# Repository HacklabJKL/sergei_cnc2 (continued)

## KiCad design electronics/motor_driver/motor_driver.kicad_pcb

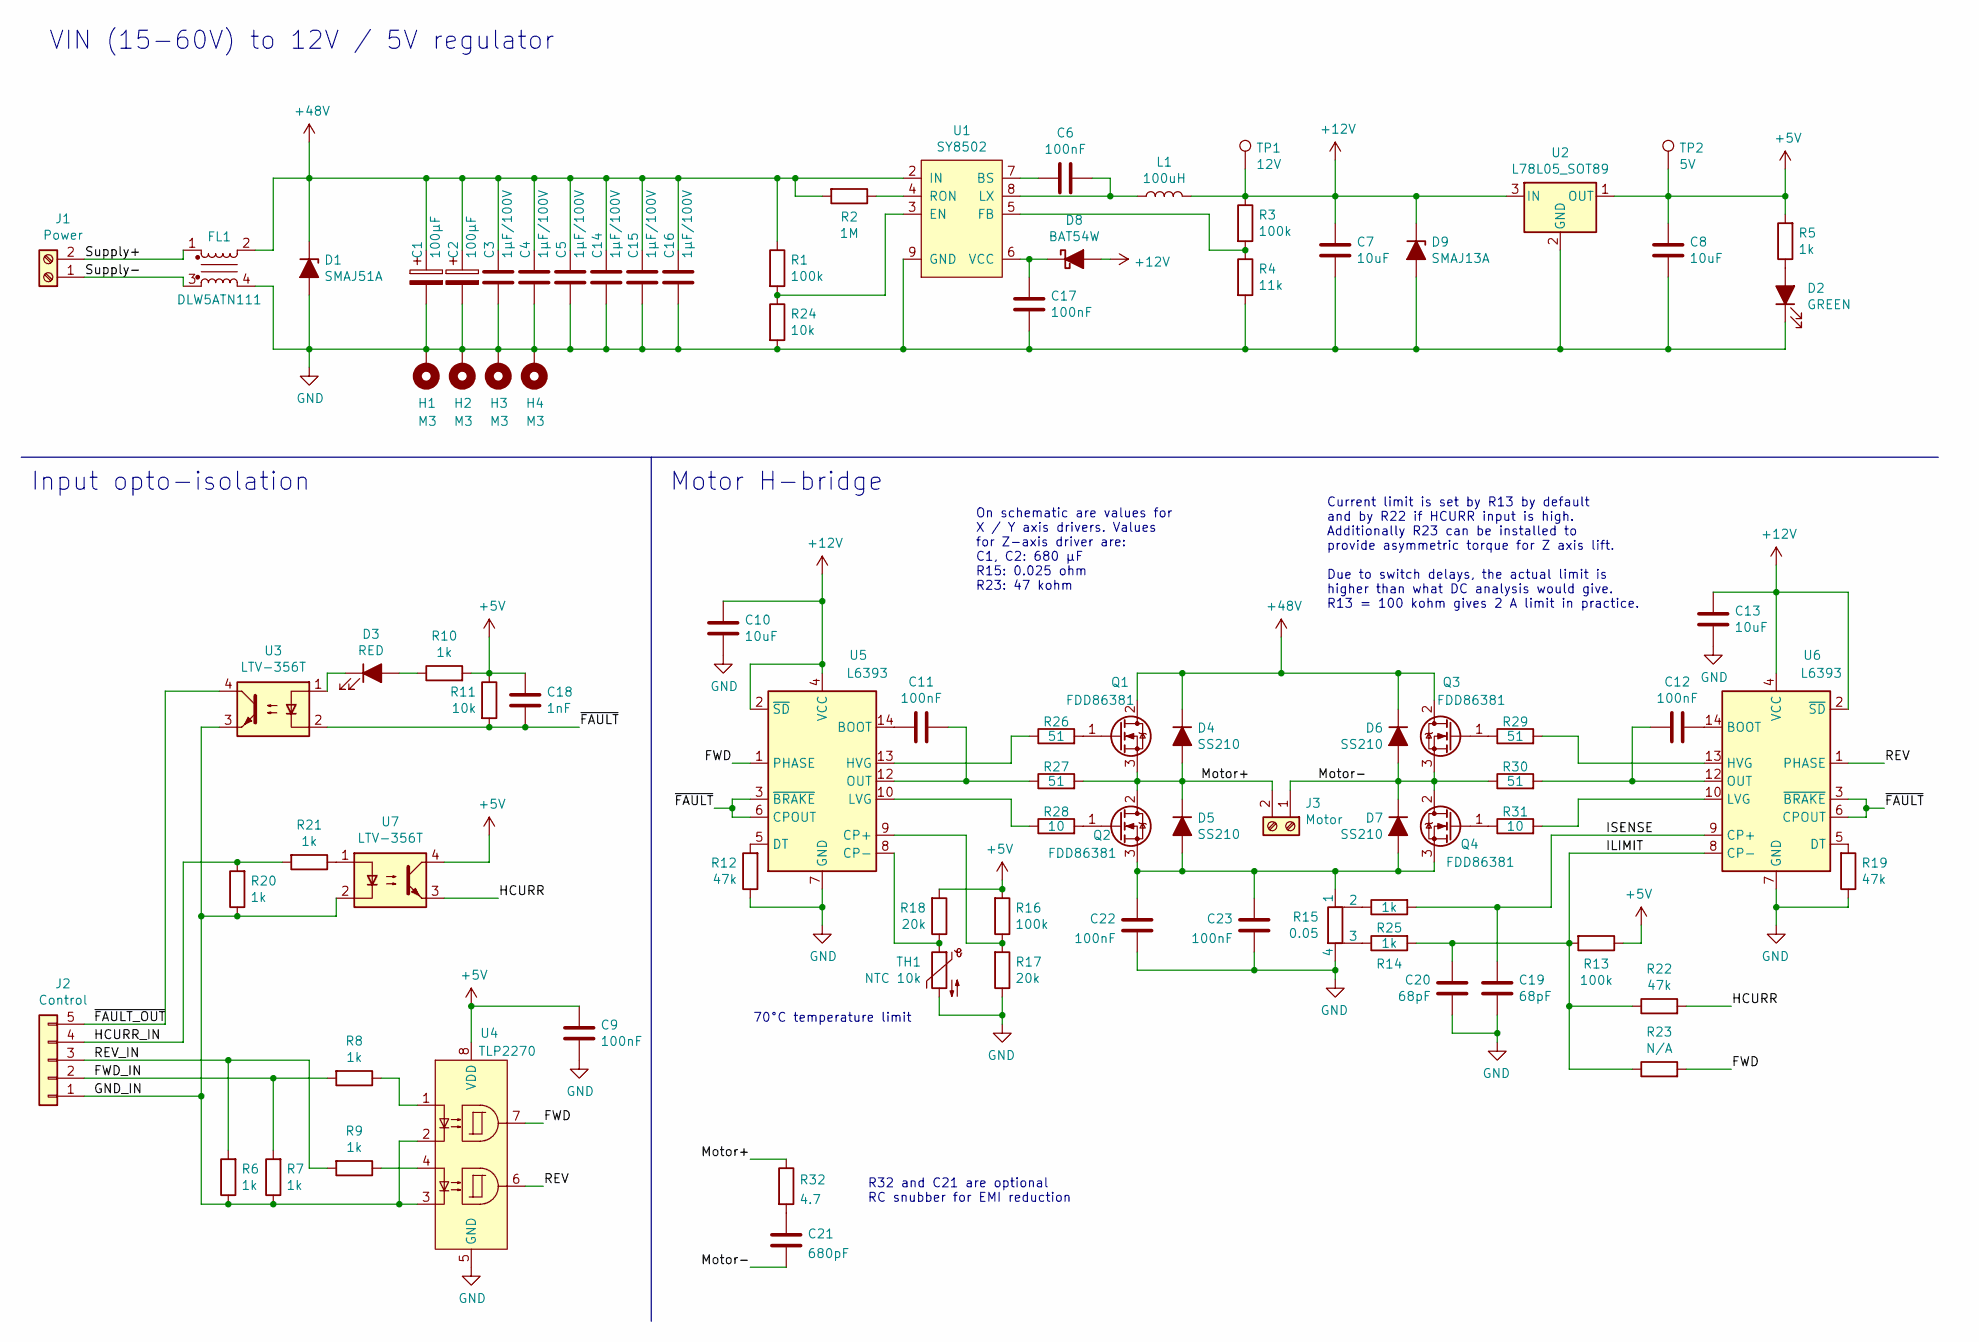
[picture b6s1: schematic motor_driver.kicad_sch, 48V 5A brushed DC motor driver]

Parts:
C1, C2: 100µF; CP_Radial_D10.0mm_P5.00mm_P7.50mm
C3, C4, C5, C14, C15, C16: 1µF/100V; C_1206_3216Metric
C6, C9, C11, C12, C17, C22, C23: 100nF; C_0603_1608Metric
C7, C8, C10, C13: 10uF; C_0805_2012Metric
C18: 1nF; C_0603_1608Metric
C19, C20: 68pF; C_0603_1608Metric
C21: 680pF; C_0805_2012Metric
D1: SMAJ51A; D_SMA
D2: GREEN; LED_0805_Reverse
D3: RED; LED_0805_Reverse
D4, D5, D6, D7: SS210; D_SMA
D8: BAT54W; D_SOD-123
D9: SMAJ13A; D_SMA
FL1: DLW5ATN111
H1, H2, H3, H4: M3; MountingHole_3.2mm_M3_Pad
J1: Power; TerminalBlock_bornier-2_P5.08mm
J2: Control; TerminalBlock_TE_282834-5_1x05_P2.54mm_Horizontal
J3: Motor; TerminalBlock_bornier-2_P5.08mm
L1: 100uH; L_Bourns-SRN4018
Q1, Q2, Q3, Q4: FDD86381; TO-252-2
R1, R3, R13, R16: 100k; R_0603_1608Metric
R2: 1M; R_0603_1608Metric
R4: 11k; R_0603_1608Metric
R5, R6, R7, R8, R9, R10, R14, R20, R21, R25: 1k; R_0603_1608Metric
R11, R24: 10k; R_0603_1608Metric
R12, R19, R22: 47k; R_0603_1608Metric
R15: 0.05; Shunt_2512
R17, R18: 20k; R_0603_1608Metric
R23: N/A; R_0603_1608Metric
R26, R27, R29, R30: 51; R_0603_1608Metric
R28, R31: 10; R_0603_1608Metric
R32: 4.7; R_0805_2012Metric
TH1: NTC 10k; R_0603_1608Metric
TP1: 12V; TestPoint_Pad_D2.0mm
TP2: 5V; TestPoint_Pad_D2.0mm
U1: SY8502; SOIC-8-1EP_3.9x4.9mm_P1.27mm_EP2.514x3.2mm
U2: L78L05_SOT89; SOT-89-3
U3, U7: LTV-356T; SO-4_4.4x3.6mm_P2.54mm
U4: TLP2270; SOIC-8_7.5x5.85mm_P1.27mm
U5, U6: L6393; SO-14_3.9x8.65mm_P1.27mm

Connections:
+5V: C8.1, C9.1, C18.1, R5.2, R10.2, R11.1, R13.1, R16.2, R18.2, TP2.1, U2.1 (OUT), U4.8 (VDD), U7.4
+12V: C7.1, C10.1, C13.1, D8.2 (A), D9.1 (K), L1.1, R3.1, TP1.1, U2.3 (IN), U5.2 (~SD), U5.4 (VCC), U6.2 (~SD), U6.4 (VCC)
+48V: C1.1, C2.1, C3.1, C4.1, C5.1, C14.1, C15.1, C16.1, D1.1 (K), D4.1 (K), D6.1 (K), FL1.2, Q1.2 (D), Q3.2 (D), R1.1, R2.2, U1.2 (IN)
/FWD: R23.2, U4.7, U5.1 (PHASE)
/FWD_IN: J2.2, R7.2, R8.2
/GND_IN: J2.1, R6.1, R7.1, R20.1, U3.3, U4.2, U4.3, U7.2
/HCURR: R22.2, U7.3
/HCURR_IN: J2.4, R20.2, R21.2
/ILIMIT: C20.1, R13.2, R14.2, R22.1, R23.1, U6.8 (CP-)
/ISENSE: C19.1, R25.2, U6.9 (CP+)
/Motor+: D4.2 (A), D5.1 (K), J3.2, Q1.3 (S), Q2.2 (D), R27.2, R32.1
/Motor-: C21.2, D6.2 (A), D7.1 (K), J3.1, Q3.3 (S), Q4.2 (D), R30.1
/REV: U4.6, U6.1 (PHASE)
/REV_IN: J2.3, R6.2, R9.2
/Supply+: FL1.1, J1.2
/Supply-: FL1.3, J1.1
/~FAULT_OUT: J2.5, U3.4
/~FAULT: C18.2, R11.2, U3.2, U5.3 (~BRAKE), U5.6 (CPOUT), U6.3 (~BRAKE), U6.6 (CPOUT)
GND: C1.2, C2.2, C3.2, C4.2, C5.2, C7.2, C8.2, C9.2, C10.2, C13.2, C14.2, C15.2, C16.2, C17.1, C19.2, C20.2, C22.2, C23.2, D1.2 (A), D2.1 (K), D9.2 (A), FL1.4, H1.1, H2.1, H3.1, H4.1, R4.2, R12.1, R15.4, R17.1, R19.1, R24.2, TH1.2, U1.9 (GND), U2.2 (GND), U4.5 (GND), U5.7 (GND), U6.7 (GND)
unnamed: C6.1, L1.2, U1.8 (LX)
unnamed: C6.2, U1.7 (BS)
unnamed: C11.1, R27.1, U5.12 (OUT)
unnamed: C11.2, U5.14 (BOOT)
unnamed: C12.1, R30.2, U6.12 (OUT)
unnamed: C12.2, U6.14 (BOOT)
unnamed: C17.2, D8.1 (K), U1.6 (VCC)
unnamed: C21.1, R32.2
unnamed: D2.2 (A), R5.1
unnamed: D3.1 (K), U3.1
unnamed: D3.2 (A), R10.1
unnamed: C22.1, C23.1, D5.2 (A), D7.2 (A), Q2.3 (S), Q4.3 (S), R15.1
unnamed: Q1.1 (G), R26.2
unnamed: Q2.1 (G), R28.2
unnamed: Q3.1 (G), R29.1
unnamed: Q4.1 (G), R31.1
unnamed: R1.2, R24.1, U1.3 (EN)
unnamed: R2.1, U1.4 (RON)
unnamed: R3.2, R4.1, U1.5 (FB)
unnamed: R8.1, U4.1
unnamed: R9.1, U4.4
unnamed: R12.2, U5.5 (DT)
unnamed: R14.1, R15.3
unnamed: R15.2, R25.1
unnamed: R16.1, R17.2, U5.9 (CP+)
unnamed: R18.1, TH1.1, U5.8 (CP-)
unnamed: R19.2, U6.5 (DT)
unnamed: R21.1, U7.1
unnamed: R26.1, U5.13 (HVG)
unnamed: R28.1, U5.10 (LVG)
unnamed: R29.2, U6.13 (HVG)
unnamed: R31.2, U6.10 (LVG)

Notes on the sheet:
Input opto-isolation
VIN (15-60V) to 12V / 5V regulator
Current limit is set by R13 by default and by R22 if HCURR input is high. Additionally R23 can be installed to provide asymmetric torque for Z axis lift. Due to switch delays, the actual limit is higher than what DC analysis would give. R13 = 100 kohm gives 2 A limit in practice.
70°C temperature limit
Motor H-bridge
R32 and C21 are optional RC snubber for EMI reduction
On schematic are values for X / Y axis drivers. Values for Z-axis driver are: C1, C2: 680 µF R15: 0.025 ohm R23: 47 kohm

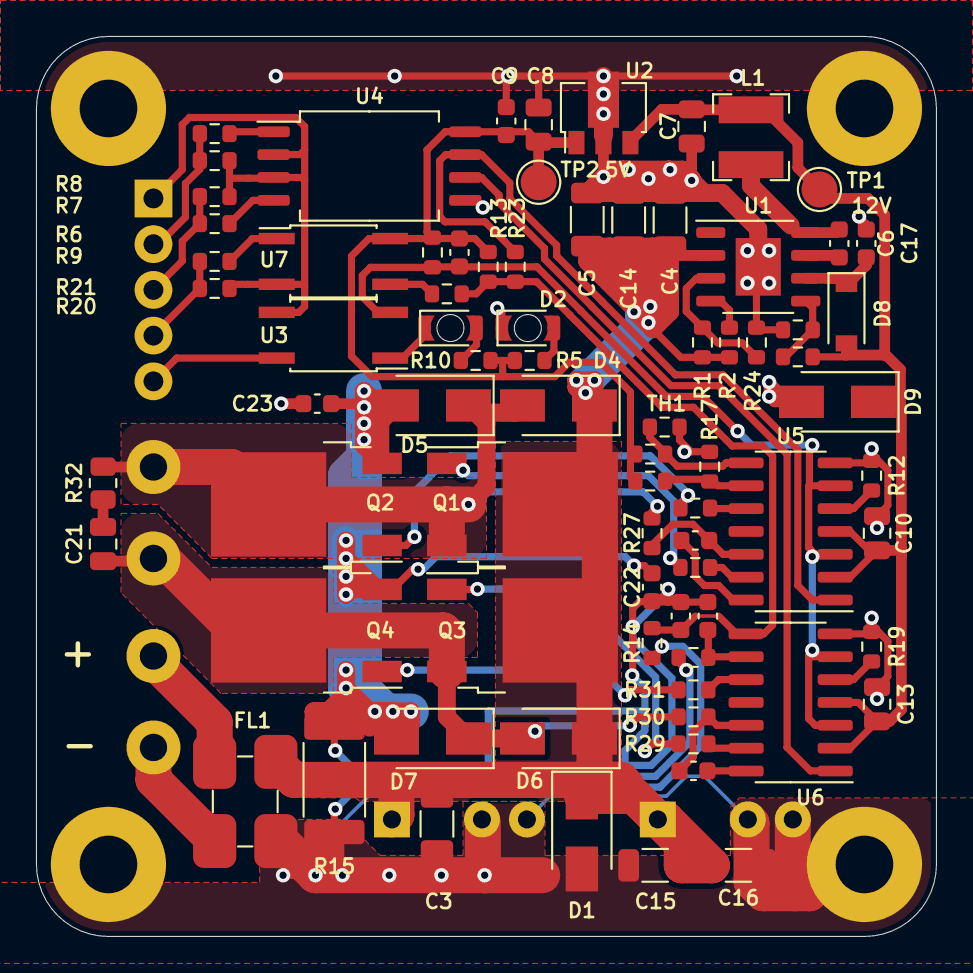
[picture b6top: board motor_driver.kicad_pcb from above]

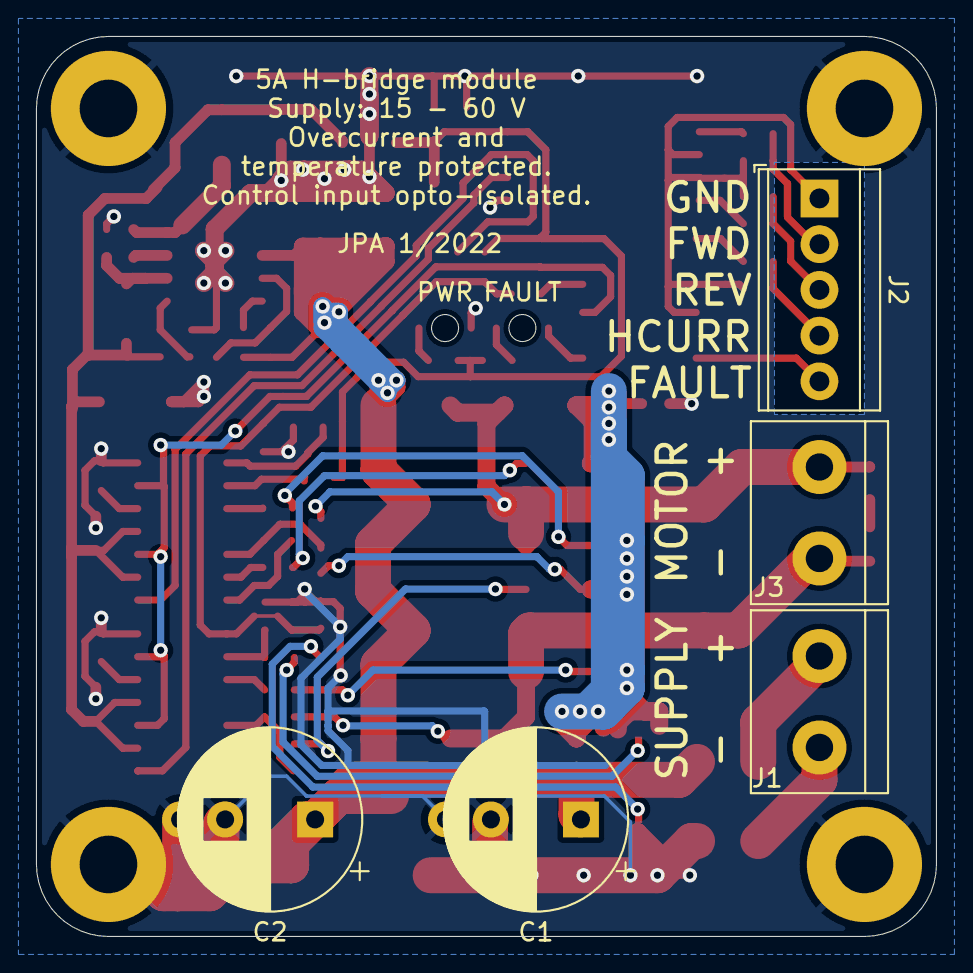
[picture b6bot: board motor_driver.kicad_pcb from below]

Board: 2 copper layers, 50.0 x 50.0 mm, 87 parts (5 on the bottom side), 51 nets.

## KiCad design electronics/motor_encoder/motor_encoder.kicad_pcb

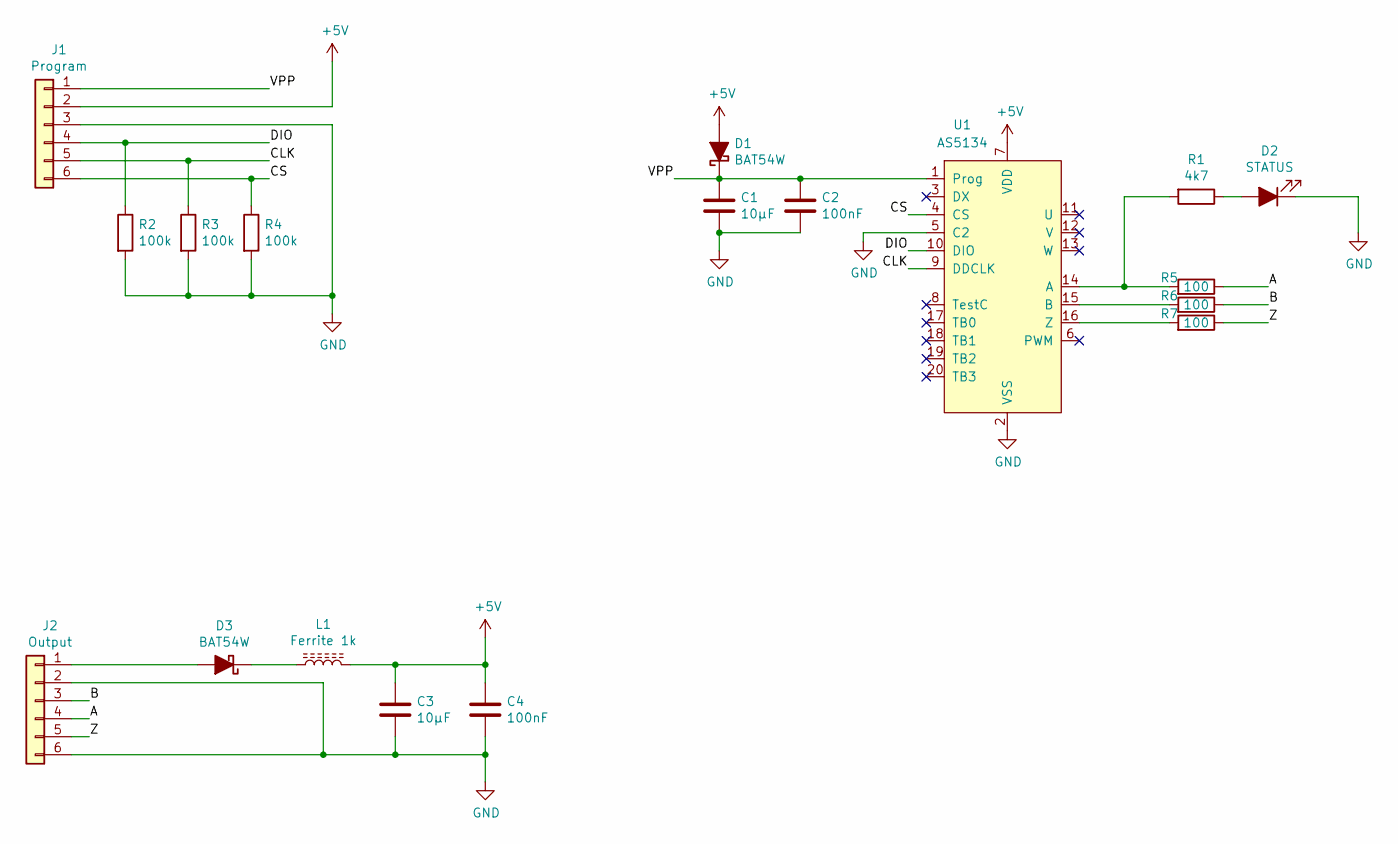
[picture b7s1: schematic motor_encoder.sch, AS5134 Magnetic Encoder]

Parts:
C1, C3: 10µF; C_0603_1608Metric
C2, C4: 100nF; C_0603_1608Metric
D1, D3: BAT54W; D_SOD-123
D2: STATUS; LED_0805_2012Metric
J1: Program; PinHeader_1x06_P2.54mm_Vertical
J2: Output; PinHeader_1x06_P2.54mm_Horizontal
L1: Ferrite 1k; L_0603_1608Metric
R1: 4k7; R_0603_1608Metric
R2, R3, R4: 100k; R_0603_1608Metric
R5, R6, R7: 100; R_0603_1608Metric
U1: AS5134; SSOP-20_5.3x7.2mm_P0.65mm

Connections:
+5V: C3.1, C4.1, D1.2 (A), J1.2, L1.2, U1.7 (VDD)
/A: J2.4, R5.1
/B: J2.3, R6.1
/CLK: J1.5, R3.1, U1.9 (DDCLK)
/CS: J1.6, R4.1, U1.4 (CS)
/DIO: J1.4, R2.1, U1.10 (DIO)
/VPP: C1.1, C2.1, D1.1 (K), J1.1, U1.1 (Prog)
/Z: J2.5, R7.1
GND: C1.2, C2.2, C3.2, C4.2, D2.1 (K), J1.3, J2.2, J2.6, R2.2, R3.2, R4.2, U1.2 (VSS), U1.5 (C2)
unnamed: D2.2 (A), R1.1
unnamed: D3.1 (K), L1.1
unnamed: D3.2 (A), J2.1
unnamed: R1.2, R5.2, U1.14 (A)
unnamed: R6.2, U1.15 (B)
unnamed: R7.2, U1.16 (Z)

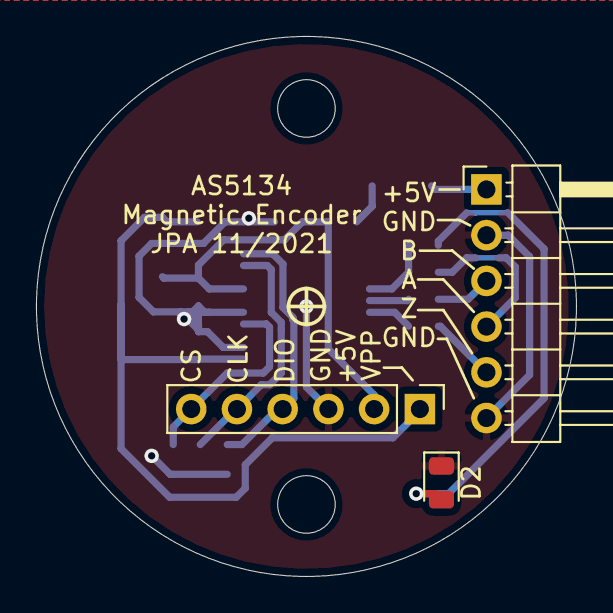
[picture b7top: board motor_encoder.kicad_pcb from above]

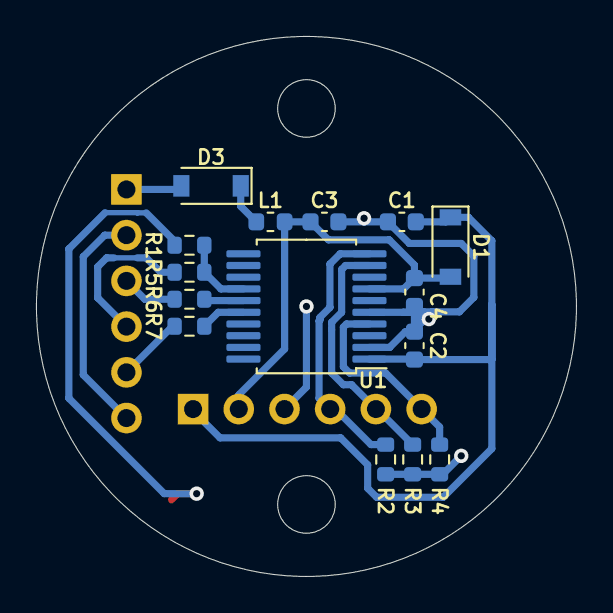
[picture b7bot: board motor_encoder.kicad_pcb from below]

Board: 2 copper layers, 30.0 x 30.0 mm, 18 parts (15 on the bottom side), 15 nets.

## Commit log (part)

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2021-11-25 Add preliminary wiring diagram and parts list
2021-11-25 Import Mesa Hostmot2 firmware
2021-11-25 Add customized pinout and bitfile for Mesa 6i25 card
2021-11-27 Update wiring diagram
2021-11-28 Add LinuxCNC HAL driver for Nocturn USB controller
2021-12-30 Add old plans for the cabinet
2021-12-31 Initial LinuxCNC configuration
2021-12-31 Update FPGA bitstream
2022-01-01 Fix FPGA pin mapping
    Mesa 6i25 IO numbers do not directly map to DB25 pin numbers.
2022-01-15 Update motor driver and power control PCB designs
2022-01-29 Switch to use 5i25 config for FPGA
2022-01-30 LinuxCNC config updates
2022-03-14 Update wiring diagram & motor driver part values
2022-03-19 Initial PID tuning
2022-04-08 Update schematics
2022-04-20 Add homing config
2022-04-21 Add PID tune panel
2022-04-21 PID tuning
2022-04-23 Camera holder 3D model
2022-04-24 Motors active sign for laser cutting
2022-04-27 LinuxCNC config: add interface to hardware buttons
2022-04-27 Add camera view
2022-04-28 Z axis bellows for laser engraving
2022-04-28 hardware pins
2022-05-02 Add VFD manual
2022-05-06 bellows
2022-05-07 Add PWM output for spindle control
2022-05-07 Fix Y axis direction
2022-05-13 LinuxCNC config for spindle control
2022-05-28 Add gladevcp sidebar
2022-05-29 Drawings for lasercutting
2022-06-03 GUI and USB control functions
2022-06-04 Axis limit
2022-06-06 Add motor runaway protection
2022-06-11 Use FSESC 4.20 for driving Z axis, add brake shunt
2022-06-11 runawayprot: fix negative delta handling
2022-06-11 HAL config and PID tuning for FSESC driver
2022-06-11 Add filter for spindle-at-speed signal
2022-06-17 Copy qtvcp cameratab widget for customizations
2022-06-17 Cameratab: retry automatically
2022-06-17 Import probescreen code from https://github.com/linuxcnc-probe-screen/probe-screen-ng
2022-06-17 Misc configuration
2022-06-17 Probing config
2022-06-18 Camera retry and offset
2022-06-18 Camera offset
2022-06-25 Small config fixes
2022-07-14 Update photos
2022-07-16 Z axis tuning
2022-07-22 misc
2022-07-22 Add matrixkins for calibration
2022-07-22 Nocturn USB controller button layout
2022-07-23 Camera tab tuning
2022-07-23 Nocturn: turn off LEDs when machine is off
2022-07-23 Tool length probe
2022-07-23 XY calibration
2022-07-23 Axis fine tuning
2022-07-26 Nocturn labels
2022-07-26 Fix some jitter with hold-to-run with door open
2022-07-31 Timeout preview in AXIS
2022-08-03 Switch to custom probe screen
2022-08-05 Add probe type selection
2022-08-06 Probing fixes
2022-08-06 Import truetype-tracer from archive.org
2022-08-06 Include angle in probe results
2022-08-06 Software calibration
2022-08-06 Probe tab: angle measurements
2022-08-06 NativeCAM default project
2022-08-06 Config fixes
2022-09-22 Improve coordinate system handling, add selector buttons to sidebar
2022-09-23 Nonzero default jog speed after restart
2022-09-23 Add wiki link to readme
2022-09-24 Add FreeCAD tool library
2022-09-24 Toe clamp design
2022-09-24 LinuxCNC tool table
2022-09-24 Fix #10
2022-09-24 Disable M6 remap, fixes #15
    The remap wasn't really working anyway.
    Related: https://github.com/LinuxCNC/linuxcnc/issues/246
2022-09-24 OpenBuildsCAM config
2022-10-01 Reduce hold-to-run delay
2022-10-22 Fix tool table zero diameters
2022-10-22 Tool number labels
2022-10-22 Add workaround for LinuxCNC/linuxcnc#177 (#19)
    LinuxCNC 2.8 has a bug where emergency stop resets the G64 path
    blending tolerance. This causes excessive rounding of corners.
    It is fixed in 2.9 but I want to keep with stable version for now.
    This works around the issue by reissuing G64 P0.01 Q0.01 after
    state-on and all-homed events.
2022-10-23 Update parts list and wiring diagram
2022-10-24 Make sure M2 is run when program stopped (#16)
    Especially NativeCAM tends to switch coordinate systems.
    If the program is stopped in middle, it is preferrable
    to restore the modal settings by running M2.
2022-11-08 Add PWM channel for coolant pump
2022-11-11 GUI controls for coolant pump
2022-11-11 Limit acceleration when using lift Z button
2022-11-12 Holddown clamp
2022-11-12 FPGA firmware: add coolant pump PWM (fix prev. commit)
2022-11-12 Coolant pump PWM config
2022-11-18 Simplify spindle monitoring, avoid false errors
2022-11-18 Fix coolant auto functionality
2022-11-25 Return Z axis as two pin PWM config
    Switching to better isolator & ADC input for FSESC.
2022-11-26 Z motor tuning
2022-12-10 Workaround problems with Z axis driver
2022-12-16 Update probe port in wiring diagram.
    Switching to 3.5mm jack to provide power to 3D probe.
2023-01-07 Updated Z motor driver settings
2023-01-07 Less aggressive Z PID
2023-01-07 Reduce Z jog acceleration back
2023-01-07 Add delay to power_enable after estop
2023-01-15 Add debounce filtering to button inputs
    Fixes some EMI issues where VFD causes spurious pulses
    to lines that rely on pull-up resistor.
2023-01-15 Remove Z coordinate from camera tab
2023-01-15 Update probing config
2023-01-21 Camera, probe settings
2023-01-23 Add remaining time to Axis status bar
2023-01-23 Show informative messages in sidebar
2023-01-23 Reduce tab widths
2023-01-24 Show notification when coordinate system changes and file is not yet reloaded
2023-01-28 nativecam template
2023-01-28 sidebar messages
2023-01-28 Coolant pump testing
2023-01-30 Improvements for lift_z functionality
    - Pause when door open
    - Workaround Z max limit not working (LinuxCNC/linuxcnc#2316)
    - Add notification to sidebar
2023-01-30 Dont start spindle when probe connected
2023-01-30 Adjust gladevcp coolant labels
2023-01-31 Better estop/power logic
    Re-enable power only by manual action after e-stop.
    This way any fault state results in hardware power-off
    until user checks things out.
2023-02-04 Power control fixes
2023-02-04 Recalibration
2023-02-10 Buck regulator PCB
2023-02-11 FlatCAM config
2023-02-11 Cooland fluid pump settings
2023-02-12 Buck regulator errata
2023-03-26 Update offset for new camera
    Also added way to set the optical center of the camera
    (as aligned with the machine Z axis).
    This allows precise measurements at any height.
2023-05-05 tutorials
2023-05-06 Coolant pump adjustment
2023-05-06 threadmill toolpath script
2023-05-20 Adjust fluid pump PWM
2023-06-17 Nocturn: Small fixes
    - Fix LED behavior in corner cases
    - Avoid GUI warnings if button is pressed too soon
2023-06-17 Add pulsed air mode
2023-06-17 Make fluid control manual for now
2023-08-05 Stepper for coolant fluid
2023-12-02 Add basic OBS streaming
2024-02-03 Operating minute counter
2024-02-03 Fix coolant pump activation when air is in pulse mode
2024-03-27 Improve runtime estimate accuracy
    Traverse moves were calculated incorrectly and axis max vel/accel was not taken into account.
2024-03-27 Don't notify about coordinate system changes when running a program.
    Otherwise G54/G55 etc. changes cause spurious messages.
2024-04-05 Beginnings of Z mapping support
2024-04-06 Z offset fixes
2024-04-07 KiriMoto profiili
2024-04-13 Fix divide by zero in remaining time calculation
2024-04-13 Laserweb profile
2024-05-17 DIN rail mounts
2024-05-17 Adjust clip distance
2024-05-17 Cable labels
2024-05-18 DIN rail mount: Ensure access to clip
2024-05-19 Update DINrail_Clip dimensions for better fit
2024-06-18 Recalibration after move to laser room
2024-06-18 Increase X axis runawayprot threshold, seem to get false triggers
2024-08-17 Adjust runawayprot thresholds
    X-axis was getting spurious triggers when matrixkins moves it very slowly.
2024-11-01 Basic T-nut for the aluminum profiles
2024-11-02 Set matrixkins Z calibration based on bed, not spindle.
    This is more useful in practice.
2024-11-14 Add spindle speed sensor & extra fan (#11, #20)
    This should allow monitoring the spindle load level and
    to cool it better at low RPM.
2024-11-15 FPGA: add encoder input for spindle speed
2024-11-15 Add intake filter for spindle fan
2024-11-15 Disable axis GUI keybindings
    The physical buttons are better and it is too easy to hit keys accidentally.
2024-11-15 Spindle speed sensor
2024-11-16 FPGA pinout fix
    Encoder 3, not 0
2024-11-16 Fix FPGA pinout
    Encoder input seems to require both pins defined.
2024-11-16 Spindle load measurement bugfixes
2024-11-22 More sturdy mount for Z carriages
2025-01-04 Recalibration after Z mounting plate replacement
2025-01-18 Increase PID deadband to stop vibrations when idle
2025-01-18 More filtering for spindle signal
2025-01-25 Median9 bugfix
2025-02-01 Add hall sensor magnet plate for spindle
2025-02-01 Updated spindle magnet mount
    Spindle speed sensor now uses OH137 hall sensor.
    Fixes #23
2025-03-29 Add toggle button for disabling squareness compensation
2025-07-19 FPGA: Use IO19 in place of broken IO28
    Got a voltage spike when hotplugging stuff
    and broke the IO pin on 6i25.
2025-07-24 Spindle fan: Add holder for Electrolux EF150 filters
    Should be more effective and easier to clean than the previous filter.
2025-11-06 1:16 input mux
2025-11-07 Input mux din rail mount
2026-06-27 Update camera offset
